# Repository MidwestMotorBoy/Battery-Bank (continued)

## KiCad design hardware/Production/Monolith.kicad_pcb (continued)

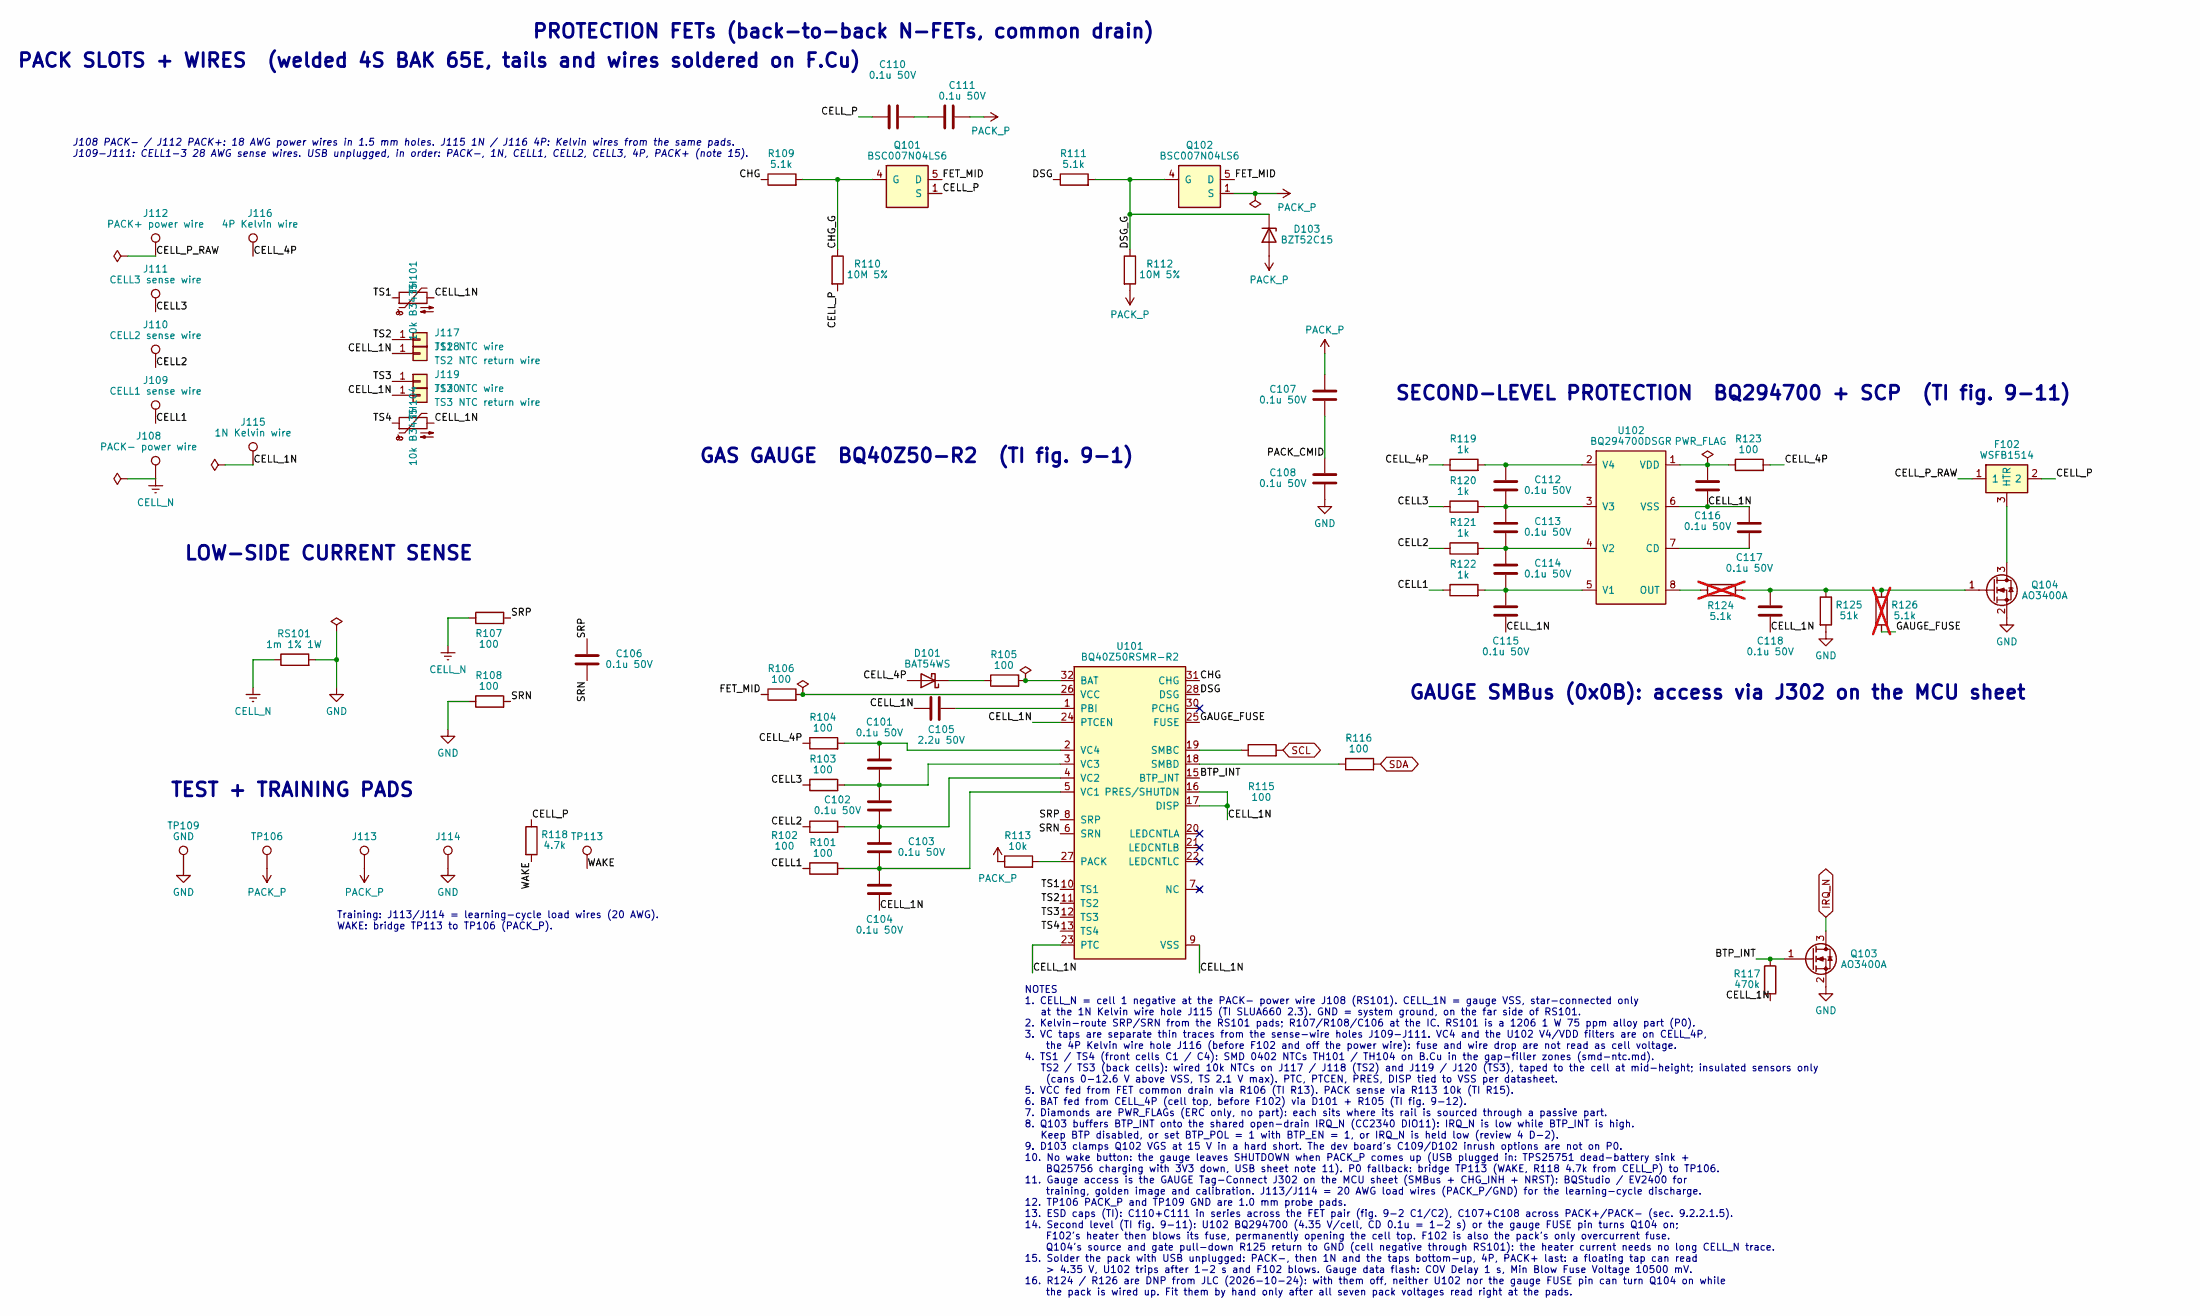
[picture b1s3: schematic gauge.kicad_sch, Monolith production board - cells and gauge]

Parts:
C101, C102, C103, C104, C106, C107, C108, C110, C111, C112, C113, C114, C115, C116, C117, C118: 0.1u 50V; C_0402_1005Metric; MPN CL05B104KB54PNC; LCSC C307331
C105: 2.2u 50V; C_0805_2012Metric; MPN CL21A225KBQNNNE; LCSC C377773
D101: BAT54WS; D_SOD-882; MPN BAT54L,315 (Nexperia); LCSC C549279
D103: BZT52C15; D_SOD-123; MPN BZT52C15 (JLC preferred C19077412); LCSC C19077412
F102: WSFB1514; TLC_WSFB_4x3mm; MPN TLC Electronic WSFB1514; LCSC C42463217
J108: PACK- power wire; SolderWire-18AWG_PTFE_1x01_D1.5mm_OD2.3mm
J109: CELL1 sense wire; SolderWire-28AWG_PTFE_1x01_D0.8mm_Pad1.5x1.4mm
J110: CELL2 sense wire; SolderWire-28AWG_PTFE_1x01_D0.8mm_Pad1.5x1.4mm
J111: CELL3 sense wire; SolderWire-28AWG_PTFE_1x01_D0.8mm_Pad1.5x1.4mm
J112: PACK+ power wire; SolderWire-18AWG_PTFE_1x01_D1.5mm_OD2.3mm
J113: LOAD PACK_P; SolderWire-0.5sqmm_1x01_D0.9mm_OD2.1mm
J114: LOAD GND; SolderWire-0.5sqmm_1x01_D0.9mm_OD2.1mm
J115: 1N Kelvin wire; SolderWire-28AWG_PTFE_1x01_D0.8mm_Pad1.5x1.4mm
J116: 4P Kelvin wire; SolderWire-28AWG_PTFE_1x01_D0.8mm_Pad1.5x1.4mm
J117: TS2 NTC wire; SolderWire-28AWG_PTFE_1x01_D0.8mm_Pad1.5x1.4mm
J118: TS2 NTC return wire; SolderWire-28AWG_PTFE_1x01_D0.8mm_Pad1.5x1.4mm
J119: TS3 NTC wire; SolderWire-28AWG_PTFE_1x01_D0.8mm_Pad1.5x1.4mm
J120: TS3 NTC return wire; SolderWire-28AWG_PTFE_1x01_D0.8mm_Pad1.5x1.4mm
Q101, Q102: BSC007N04LS6; Infineon_PG-TDSON-8_6.15x5.15mm_D5-8; MPN BSC007N04LS6ATMA1 (Infineon); LCSC C534274
Q103, Q104: AO3400A; SOT-23; MPN AO3400A (AOS); LCSC C20917
R101, R102, R103, R104, R105, R106, R107, R108, R123: 100; R_0402_1005Metric; MPN 0402WGF1000TCE; LCSC C25076
R109, R111: 5.1k; R_0402_1005Metric; MPN 0402WGF5101TCE; LCSC C25905
R110, R112: 10M 5%; R_0402_1005Metric; MPN 0402WGJ0106TCE; LCSC C26086
R113: 10k; R_0402_1005Metric; MPN 0402WGF1002TCE; LCSC C25744
R115, R116: 100; R_0201_0603Metric; MPN 0201WMF1000TEE; LCSC C270366
R117: 470k; R_0402_1005Metric; MPN 0402WGF4703TCE; LCSC C25790
R118: 4.7k; R_0402_1005Metric; MPN 0402WGF4701TCE; LCSC C25900
R119, R120, R121, R122: 1k; R_0402_1005Metric; MPN 0402WGF1001TCE; LCSC C11702
R124, R126: 5.1k; R_0402_1005Metric; MPN 0402WGF5101TCE; LCSC C25905; not fitted
R125: 51k; R_0402_1005Metric; MPN 0402WGF5102TCE; LCSC C25794
RS101: 1m 1% 1W; R_1206_3216Metric; MPN LR1206-21R001F4 (Ralec, 75 ppm); LCSC C154629
TH101, TH104: 10k B3435; R_0402_1005Metric; MPN NCP15XH103F03RC; LCSC C77131
TP106: PACK_P; TestPoint_Pad_D1.0mm
TP109: GND; TestPoint_Pad_D1.0mm; MPN RH-S2761-46R (ronghe; Harwin S2761-46R 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
TP113: WAKE; TestPoint_Pad_D1.0mm
U101: BQ40Z50RSMR-R2; TI_RSM0032A_VQFN-32_4x4mm_P0.4mm_EP1.4x1.4mm; MPN BQ40Z50RSMR-R2; LCSC C2845123
U102: BQ294700DSGR; Texas_DSG0008A_WSON-8-1EP_2x2mm_P0.5mm_EP0.9x1.6mm; MPN BQ294700DSGR; LCSC C414622

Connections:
/Cells and Gauge/BTP_INT: Q103.1 (G), R117.1, U101.15 (BTP_INT)
/Cells and Gauge/CELL1: J109.1 (1_1), R101.1, R122.1
/Cells and Gauge/CELL2: J110.1 (1_1), R102.1, R121.1
/Cells and Gauge/CELL3: J111.1 (1_1), R103.1, R120.1
/Cells and Gauge/CELL_1N: C104.2, C105.2, C115.2, C116.2, C117.1, C118.2, J115.1 (1_1), J118.1 (Pin_1_1), J120.1 (Pin_1_1), R117.2, TH101.2, TH104.2, U101.9 (VSS), U101.16 (PRES/SHUTDN), U101.17 (DISP), U101.23 (PTC), U101.24 (PTCEN), U101.33 (VSS), U102.6 (VSS), U102.9 (VSS)
/Cells and Gauge/CELL_4P: D101.2 (A), J116.1 (1_1), R104.1, R119.1, R123.2
/Cells and Gauge/CELL_P: C110.1, F102.2, Q101.1 (S), Q101.2 (S), Q101.3 (S), R110.2, R118.1
/Cells and Gauge/CELL_P_RAW: F102.1, J112.1 (1_1)
/Cells and Gauge/CHG: R109.1, U101.31 (CHG)
/Cells and Gauge/CHG_G: Q101.4 (G), R109.2, R110.1
/Cells and Gauge/DSG: R111.1, U101.28 (DSG)
/Cells and Gauge/DSG_G: D103.1 (K), Q102.4 (G), R111.2, R112.1
/Cells and Gauge/FET_MID: Q101.5 (D), Q101.6 (D), Q101.7 (D), Q101.8 (D), Q102.5 (D), Q102.6 (D), Q102.7 (D), Q102.8 (D), R106.1
/Cells and Gauge/GAUGE_FUSE: R126.2, U101.25 (FUSE)
/Cells and Gauge/PACK_CMID: C107.2, C108.1
/Cells and Gauge/SRN: C106.2, R108.2, U101.6 (SRN)
/Cells and Gauge/SRP: C106.1, R107.2, U101.8 (SRP)
/Cells and Gauge/TS1: TH101.1, U101.10 (TS1)
/Cells and Gauge/TS2: J117.1 (Pin_1_1), U101.11 (TS2)
/Cells and Gauge/TS3: J119.1 (Pin_1_1), U101.12 (TS3)
/Cells and Gauge/TS4: TH104.1, U101.13 (TS4)
/Cells and Gauge/WAKE: R118.2, TP113.1 (1_1)
CELL_N: J108.1 (1_1), R107.1, RS101.1
GND: C108.2, J114.1 (1_1), Q103.2 (S), Q104.2 (S), R108.1, R125.2, RS101.2, TP109.1 (1_1); also elsewhere on the board
IRQ_N: Q103.3 (D); also elsewhere on the board
unnamed: C110.2, C111.1
unnamed: D101.1 (K), R105.1
unnamed: F102.3 (HTR), Q104.3 (D)
unnamed: C118.1, Q104.1 (G), R124.2, R125.1, R126.1
unnamed: R105.2, U101.32 (BAT)
unnamed: R113.2, U101.27 (PACK)
unnamed: C105.1, U101.1 (PBI)
unnamed: R115.1, U101.19 (SMBC)
unnamed: R116.1, U101.18 (SMBD)
unnamed: C103.2, C104.1, R101.2, U101.5 (VC1)
unnamed: C102.2, C103.1, R102.2, U101.4 (VC2)
unnamed: C101.2, C102.1, R103.2, U101.3 (VC3)
unnamed: C101.1, R104.2, U101.2 (VC4)
unnamed: R106.2, U101.26 (VCC)
unnamed: C117.2, U102.7 (CD)
unnamed: R124.1, U102.8 (OUT)
unnamed: C114.2, C115.1, R122.2, U102.5 (V1)
unnamed: C113.2, C114.1, R121.2, U102.4 (V2)
unnamed: C112.2, C113.1, R120.2, U102.3 (V3)
unnamed: C112.1, R119.2, U102.2 (V4)
unnamed: C116.1, R123.1, U102.1 (VDD)
PACK_P: C107.1, C111.2, D103.2 (A), J113.1 (1_1), Q102.1 (S), Q102.2 (S), Q102.3 (S), R112.2, R113.1, TP106.1 (1_1); also elsewhere on the board
SCL: R115.2; also elsewhere on the board
SDA: R116.2; also elsewhere on the board

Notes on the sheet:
LOW-SIDE CURRENT SENSE
PACK SLOTS + WIRES (welded 4S BAK 65E, tails and wires soldered on F.Cu)
NOTES 1. CELL_N = cell 1 negative at the PACK- power wire J108 (RS101). CELL_1N = gauge VSS, star-connected only at the 1N Kelvin wire hole J115 (TI SLUA660 2.3). GND = system ground, on the far side of RS101. 2. Kelvin-route SRP/SRN from the RS101 pads; R107/R108/C106 at the IC. RS101 is a 1206 1 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
GAS GAUGE BQ40Z50-R2 (TI fig. 9-1)
SECOND-LEVEL PROTECTION BQ294700 + SCP (TI fig. 9-11)
J108 PACK- / J112 PACK+: 18 AWG power wires in 1.5 mm holes. J115 1N / J116 4P: Kelvin wires from the same pads. J109-J111: CELL1-3 28 AWG sense wires. USB unplugged, in order: PACK-, 1N, CELL1, CELL2, CELL3, 4P, PACK+ (note 15).
PROTECTION FETs (back-to-back N-FETs, common drain)
TEST + TRAINING PADS
Training: J113/J114 = learning-cycle load wires (20 AWG). WAKE: bridge TP113 to TP106 (PACK_P).
GAUGE SMBus (0x0B): access via J302 on the MCU sheet

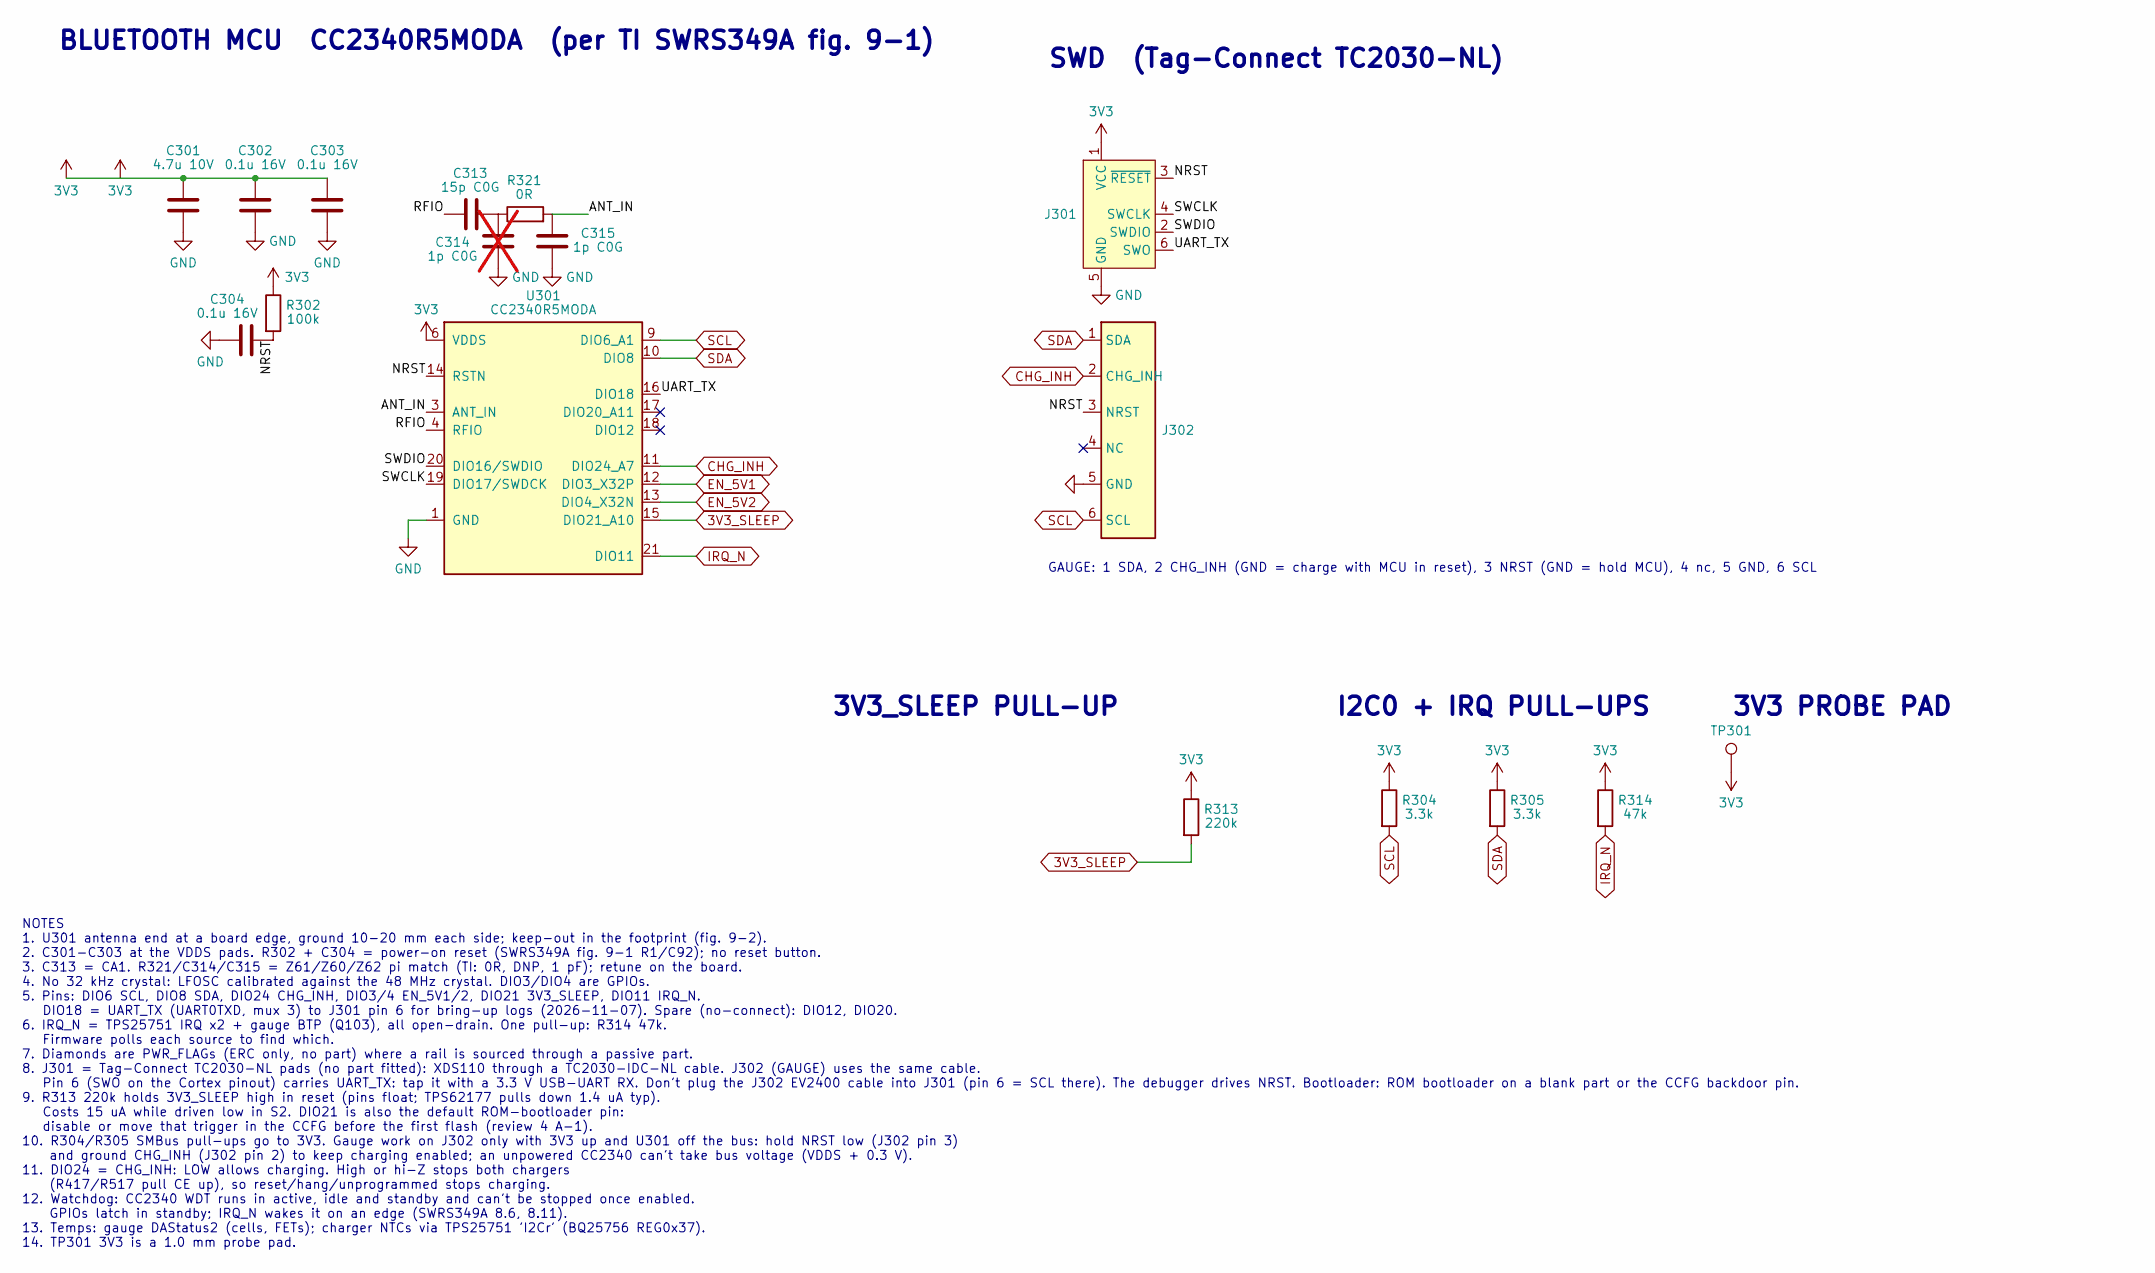
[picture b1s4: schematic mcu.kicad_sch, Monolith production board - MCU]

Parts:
C301: 4.7u 10V; C_0402_1005Metric; MPN CL05A475MP5NRNC; LCSC C23733
C302, C303, C304: 0.1u 16V; C_0201_0603Metric; MPN CL03A104KO3NNNC; LCSC C307380
C313: 15p C0G; C_0402_1005Metric; MPN 0402CG150J500NT; LCSC C1548
C314: 1p C0G; C_0402_1005Metric; MPN 0402CG1R0C500NT; LCSC C1550; not fitted
C315: 1p C0G; C_0402_1005Metric; MPN 0402CG1R0C500NT; LCSC C1550
J301: TC2030-NL; Tag-Connect_TC2030-IDC-NL_2x03_P1.27mm_Vertical
J302: TC2030-NL GAUGE; Tag-Connect_TC2030-IDC-NL_2x03_P1.27mm_Vertical
R302: 100k; R_0201_0603Metric; MPN 0201WMF1003TEE; LCSC C270364
R304, R305: 3.3k; R_0201_0603Metric; MPN 0201WMF3301TEE; LCSC C270350
R313: 220k; R_0201_0603Metric; MPN 0201WMF2203TEE; LCSC C473458
R314: 47k; R_0201_0603Metric; MPN 0201WMF4702TEE; LCSC C270345
R321: 0R; R_0402_1005Metric; MPN 0402WGF0000TCE; LCSC C17168
TP301: 3V3; TestPoint_Pad_D1.0mm
U301: CC2340R5MODA; TI_MHA0024A_CC2340R5MODA_7x10mm; MPN CC2340R5MODAN0MHAR

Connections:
3V3: C301.1, C302.1, C303.1, J301.1 (VCC), R302.1, R304.1, R305.1, R313.1, R314.1, TP301.1 (1_1), U301.6 (VDDS), U301.7 (VDDS); also elsewhere on the board
3V3_SLEEP: R313.2, U301.15 (DIO21_A10); also elsewhere on the board
/MCU/ANT_IN: C315.1, R321.2, U301.3 (ANT_IN)
/MCU/NRST: C304.1, J301.3 (~RESET), J302.3 (NRST), R302.2, U301.14 (RSTN)
/MCU/RFIO: C313.1, U301.4 (RFIO)
/MCU/SWCLK: J301.4 (SWCLK), U301.19 (DIO17/SWDCK)
/MCU/SWDIO: J301.2 (SWDIO), U301.20 (DIO16/SWDIO)
/MCU/UART_TX: J301.6 (SWO), U301.16 (DIO18)
CHG_INH: J302.2 (CHG_INH), U301.11 (DIO24_A7); also elsewhere on the board
EN_5V1: U301.12 (DIO3_X32P); also elsewhere on the board
EN_5V2: U301.13 (DIO4_X32N); also elsewhere on the board
GND: C301.2, C302.2, C303.2, C304.2, C314.2, C315.2, J301.5 (GND), J302.5 (GND), U301.1 (GND), U301.2 (GND), U301.5 (GND), U301.8 (GND), U301.22 (GND), U301.23 (GND), U301.24 (GND); also elsewhere on the board
IRQ_N: R314.2, U301.21 (DIO11); also elsewhere on the board
unnamed: C313.2, C314.1, R321.1
SCL: J302.6 (SCL), R304.2, U301.9 (DIO6_A1); also elsewhere on the board
SDA: J302.1 (SDA), R305.2, U301.10 (DIO8); also elsewhere on the board

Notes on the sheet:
NOTES 1. U301 antenna end at a board edge, ground 10-20 mm each side; keep-out in the footprint (fig. 9-2). 2. C301-C303 at the VDDS pads. R302 + C304 = power-on reset (SWRS349A fig. 9-1 R1/C92); no reset button. 3. C313 = CA1. R321/C314/C315 = Z61/Z60/Z62 pi match (TI: 0R, DNP, 1 pF); retune on th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
I2C0 + IRQ PULL-UPS
3V3_SLEEP PULL-UP
BLUETOOTH MCU CC2340R5MODA (per TI SWRS349A fig. 9-1)
3V3 PROBE PAD
GAUGE: 1 SDA, 2 CHG_INH (GND = charge with MCU in reset), 3 NRST (GND = hold MCU), 4 nc, 5 GND, 6 SCL
SWD (Tag-Connect TC2030-NL)

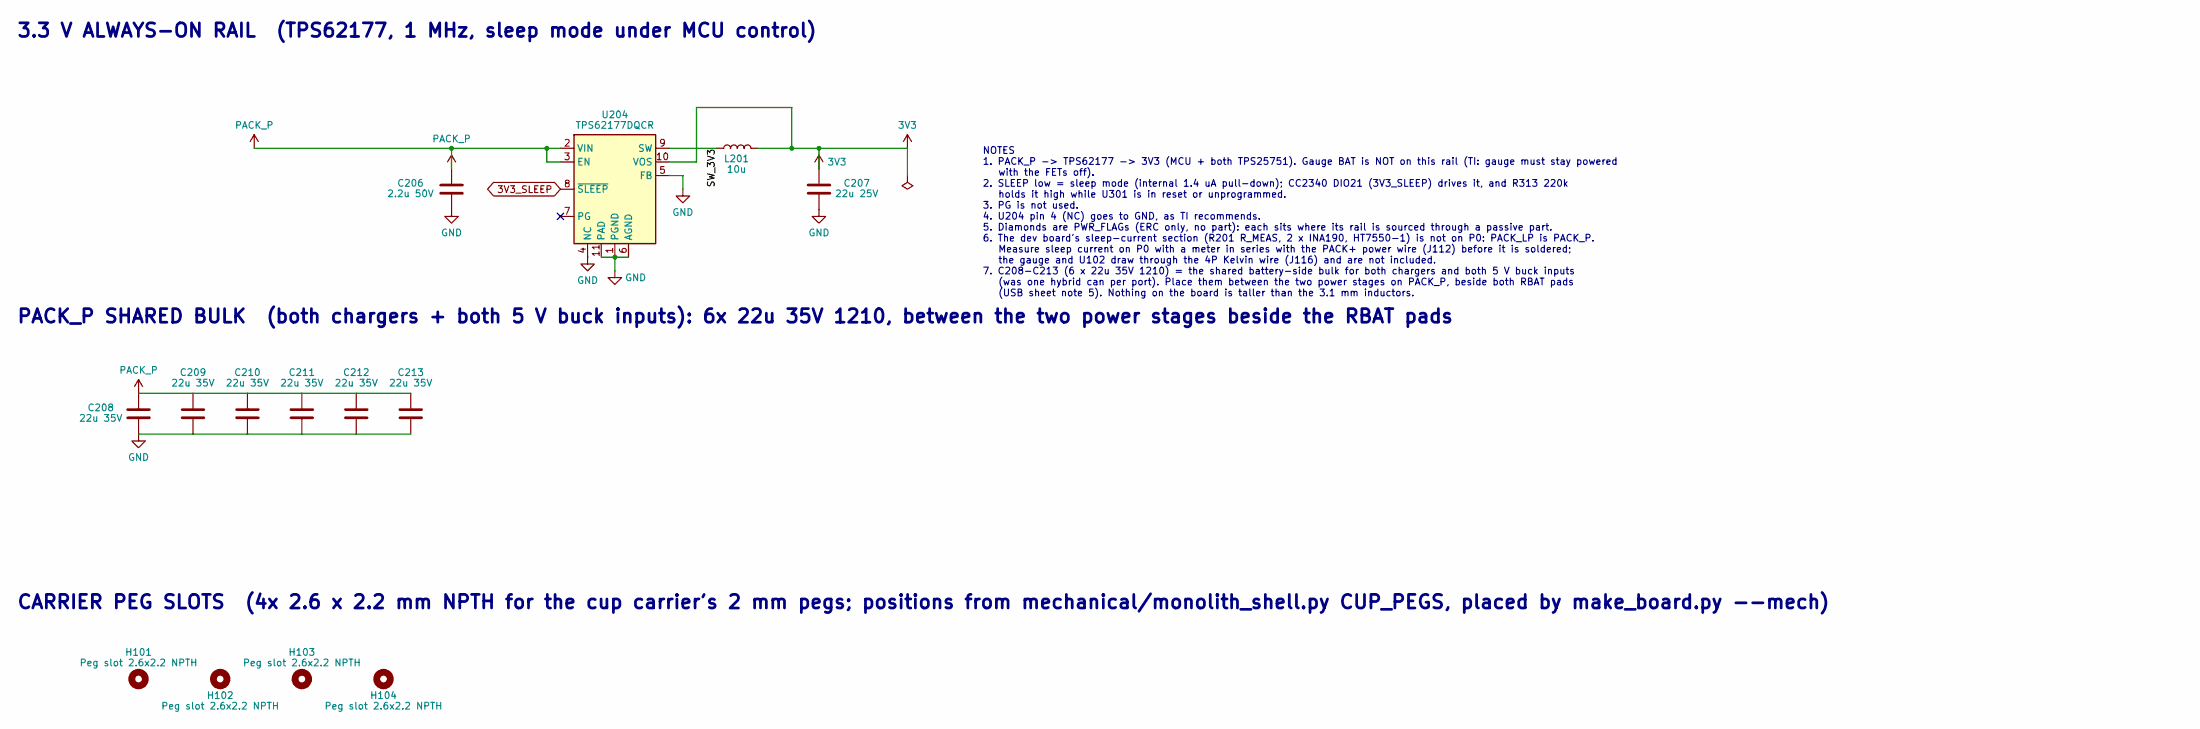
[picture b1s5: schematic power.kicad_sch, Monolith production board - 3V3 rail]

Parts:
C206: 2.2u 50V; C_0805_2012Metric; MPN CL21A225KBQNNNE; LCSC C377773
C207: 22u 25V; C_0805_2012Metric; MPN CL21A226MAQNNNE; LCSC C45783
C208, C209, C210, C211, C212, C213: 22u 35V; C_1210_3225Metric; MPN GMK325BJ226MM-P; LCSC C778721
H101, H102, H103, H104: Peg slot 2.6x2.2 NPTH; Peg_NPTH_Slot2.6x2.2mm
L201: 10u; L_Changjiang_FNR4030S; MPN FNR4030S100MT (Changjiang); LCSC C167879
U204: TPS62177DQCR; WSON-10-1EP_2x3mm_P0.5mm_EP0.84x2.4mm; MPN TPS62177DQCR; LCSC C91241

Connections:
3V3: C207.1, L201.2, U204.10 (VOS); also elsewhere on the board
3V3_SLEEP: U204.8 (~SLEEP); also elsewhere on the board
/3V3 Rail/SW_3V3: L201.1, U204.9 (SW)
GND: C206.2, C207.2, C208.2, C209.2, C210.2, C211.2, C212.2, C213.2, U204.1 (PGND), U204.4 (NC), U204.5 (FB), U204.6 (AGND), U204.11 (PAD); also elsewhere on the board
PACK_P: C206.1, C208.1, C209.1, C210.1, C211.1, C212.1, C213.1, U204.2 (VIN), U204.3 (EN); also elsewhere on the board

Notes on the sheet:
PACK_P SHARED BULK (both chargers + both 5 V buck inputs): 6x 22u 35V 1210, between the two power stages beside the RBAT pads
3.3 V ALWAYS-ON RAIL (TPS62177, 1 MHz, sleep mode under MCU control)
NOTES 1. PACK_P -> TPS62177 -> 3V3 (MCU + both TPS25751). Gauge BAT is NOT on this rail (TI: gauge must stay powered with the FETs off). 2. SLEEP low = sleep mode (internal 1.4 uA pull-down); CC2340 DIO21 (3V3_SLEEP) drives it, and R313 220k holds it high while U301 is in reset or unprogrammed. 3. 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
CARRIER PEG SLOTS (4x 2.6 x 2.2 mm NPTH for the cup carrier's 2 mm pegs; positions from mechanical/monolith_shell.py CUP_PEGS, placed by make_board.py --mech)

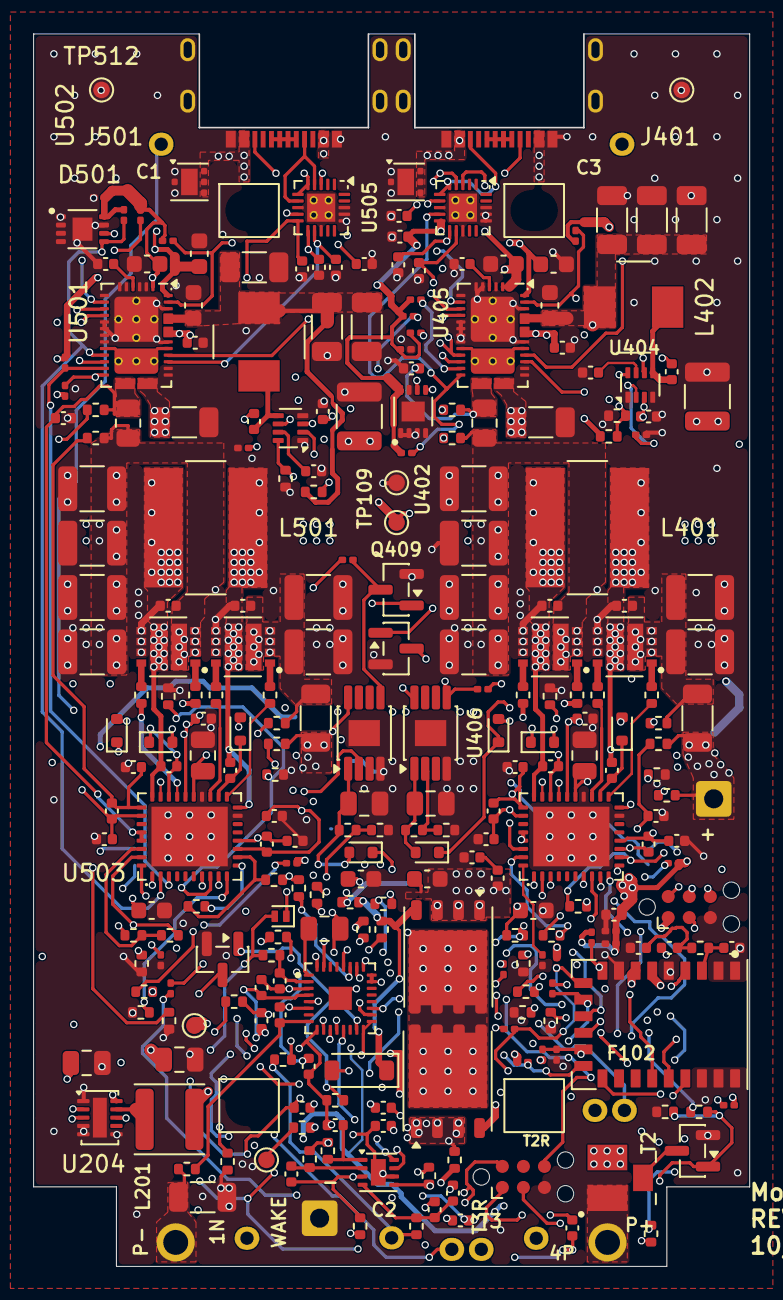
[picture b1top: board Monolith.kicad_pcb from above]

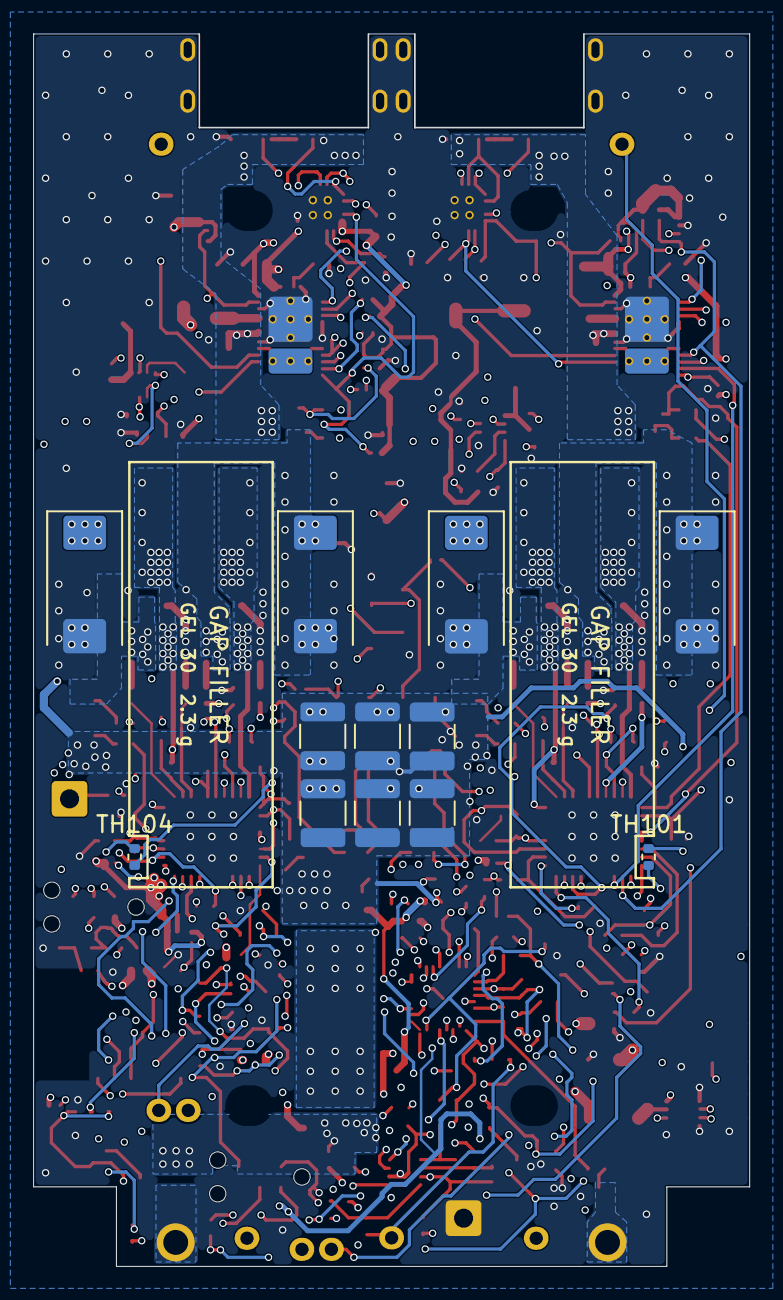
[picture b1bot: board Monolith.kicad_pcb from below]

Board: 6 copper layers, 43.2 x 74.4 mm, 289 parts (12 on the bottom side), 168 nets.

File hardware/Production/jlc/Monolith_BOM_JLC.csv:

Comment,Designator,Footprint,LCSC Part #,MPN,Qty
0.1u 50V,"C101,C102,C103,C104,C106,C107,C108,C110,C111,C112,C113,C114,C115,C116,C117,C118,C412,C413,C415,C416,C418,C419,C430,C438,C440,C446,C449,C451,C512,C513,C515,C516,C518,C519,C530,C538,C540,C546,C549,C551",C_0402_1005Metric,C307331,CL05B104KB54PNC,40
2.2u 50V,"C105,C206",C_0805_2012Metric,C377773,CL21A225KBQNNNE,2
22u 25V,"C207,C458,C558",C_0805_2012Metric,C45783,CL21A226MAQNNNE,3
22u 35V,"C208,C209,C210,C211,C212,C213,C420,C423,C424,C427,C431,C434,C444,C520,C523,C524,C527,C531,C534,C544",C_1210_3225Metric,C778721,GMK325BJ226MM-P,20
4.7u 10V,"C301,C410,C510",C_0402_1005Metric,C23733,CL05A475MP5NRNC,3
0.1u 16V,"C302,C303,C304,C408,C508",C_0201_0603Metric,C307380,CL03A104KO3NNNC,5
15p C0G,C313,C_0402_1005Metric,C1548,0402CG150J500NT,1
1p C0G,C315,C_0402_1005Metric,C1550,0402CG1R0C500NT,1
220p 50V,"C401,C402,C501,C502",C_0402_1005Metric,C1530,0402B221K500NT,4
10u 25V,"C403,C404,C407,C503,C504,C507",C_0603_1608Metric,C96446,CL10A106MA8NRNC,6
10u 6.3V,"C405,C505",C_0402_1005Metric,C15525,CL05A106MQ5NUNC,2
4.7u 50V,"C406,C506",C_1206_3216Metric,C29823,1206B475K500NT,2
1u 50V (VAC),"C409,C509",C_0603_1608Metric,C15849,CL10A105KB8NNNC,2
4.7u 25V,"C411,C511",C_0805_2012Metric,C1779,CL21A475KAQNNNE,2
0.47u 25V,"C414,C417,C514,C517",C_0402_1005Metric,C92361,CL05A474KA5NNNC,4
68u 35V,"C421,C456,C521,C556",CP_EIA-7343-31_Kemet-D,,KEMET T593V686M035APE070 (polymer tantalum),4
33n 50V,"C439,C539",C_0402_1005Metric,C7419416,FCC0402B333K500AT,2
22u 25V,"C441,C442,C443,C541,C542,C543",C_1206_3216Metric,C12891,CL31A226KAHNNNE,6
10n 50V,"C450,C550",C_0402_1005Metric,C15195,CL05B103KB5NNNC,2
1u 25V,"C452,C552",C_0402_1005Metric,C52923,CL05A105KA5NQNC,2
1u 50V,"C457,C557",C_0603_1608Metric,C15849,CL10A105KB8NNNC,2
BAT54WS,D101,D_SOD-882,C549279,"BAT54L,315 (Nexperia)",1
BZT52C15,D103,D_SOD-123,C19077412,BZT52C15 (JLC preferred C19077412),1
TVS2200DRVR,"D401,D501",WSON-6-1EP_2x2mm_P0.65mm_EP1x1.6mm,C55616459,TVS2200DRVR,2
LRB520S-40T1G,"D404,D405,D410,D411,D504,D505,D510,D511",D_SOD-523,C132124,LRB520S-40T1G,8
WSFB1514,F102,TLC_WSFB_4x3mm,C42463217,TLC Electronic WSFB1514,1
TYPE-C 16PCB1.6 IP68,"J401,J501",USB_C_Receptacle_ShouHan_TYPE-C_16PCB1.6_IP68,C55629729,TYPE-C 16PCB1.6 IP68 (Shou Han),2
10u,L201,L_Changjiang_FNR4030S,C167879,FNR4030S100MT (Changjiang),1
3.3u,"L401,L501",L_Coilank_APS0730,,XGL7030-332MEC (Coilcraft),2
3.3u,"L402,L502",L_COILMX_MS0520,C49248023,EHE05023R3MFB (ABC),2
BSC007N04LS6,"Q101,Q102",Infineon_PG-TDSON-8_6.15x5.15mm_D5-8,C534274,BSC007N04LS6ATMA1 (Infineon),2
AO3400A,"Q103,Q104,Q409,Q509",SOT-23,C20917,AO3400A (AOS),4
SiZ240DT,"Q401,Q402,Q501,Q502",Vishay_PowerPAIR_3x3S,C3289403,SiZ240DT-T1-GE3 (Vishay),4
100,"R101,R102,R103,R104,R105,R106,R107,R108,R123",R_0402_1005Metric,C25076,0402WGF1000TCE,9
5.1k,"R109,R111",R_0402_1005Metric,C25905,0402WGF5101TCE,2
10M 5%,"R110,R112",R_0402_1005Metric,C26086,0402WGJ0106TCE,2
10k,R113,R_0402_1005Metric,C25744,0402WGF1002TCE,1
100,"R115,R116",R_0201_0603Metric,C270366,0201WMF1000TEE,2
470k,R117,R_0402_1005Metric,C25790,0402WGF4703TCE,1
4.7k,R118,R_0402_1005Metric,C25900,0402WGF4701TCE,1
1k,"R119,R120,R121,R122",R_0402_1005Metric,C11702,0402WGF1001TCE,4
51k,R125,R_0402_1005Metric,C25794,0402WGF5102TCE,1
100k,"R302,R432,R441,R454,R455,R532,R541,R554,R555",R_0201_0603Metric,C270364,0201WMF1003TEE,9
3.3k,"R304,R305,R402,R403,R502,R503",R_0201_0603Metric,C270350,0201WMF3301TEE,6
220k,R313,R_0201_0603Metric,C473458,0201WMF2203TEE,1
47k,"R314,R417,R517",R_0201_0603Metric,C270345,0201WMF4702TEE,3
0R,"R321,R444,R445,R446,R447,R544,R545,R546,R547",R_0402_1005Metric,C17168,0402WGF0000TCE,9
10k,"R404,R504",R_0201_0603Metric,C473048,0201WMF1002TEE,2
137k 1%,"R409,R509",R_0402_1005Metric,C32298,0402WGF1373TCE,2
40.2k 1%,"R410,R452,R510,R552",R_0402_1005Metric,C25893,0402WGF4022TCE,4
10k 1%,"R411,R511",R_0402_1005Metric,C25744,0402WGF1002TCE,2
49.9k 1%,"R412,R512",R_0201_0603Metric,C7343965,RMCF0201FT49K9 (Stackpole),2
11.8k 1%,"R413,R513",R_0402_1005Metric,C93752,0402WGF1182TCE,2
3.6k 1%,"R414,R514",R_0402_1005Metric,C25891,0402WGF3601TCE,2
1.8k 1%,"R415,R515",R_0402_1005Metric,C25871,0402WGF1801TCE,2
5.6k 1%,"R416,R453,R516,R553",R_0402_1005Metric,C25908,0402WGF5601TCE,4
100k 0.1%,"R418,R518",R_0402_1005Metric,C445619,ERA2AEB104X,2
10.0k 0.1%,"R419,R519",R_0402_1005Metric,C191915,ERA2AEB103X,2
5m 0.5W,"R424,R524",R_0805_2012Metric,C728267,PA0805FRE470R005L,2
10R,"R425,R426,R428,R429,R525,R526,R528,R529",R_0402_1005Metric,C25077,0402WGF100JTCE,8
5m 1W (RBAT),"R427,R527",R_1206_3216Metric,C252653,MA120610FR005MZ (50 ppm),2
120k,"R433,R533",R_0402_1005Metric,C25750,0402WGF1203TCE,2
22k,"R434,R534",R_0402_1005Metric,C25768,0402WGF2202TCE,2
1k,"R435,R535",R_0201_0603Metric,C270365,0201WMF1001TEE,2
1m 1% 1W,RS101,R_1206_3216Metric,C154629,"LR1206-21R001F4 (Ralec, 75 ppm)",1
10k B3435,"TH101,TH104,TH401,TH501",R_0402_1005Metric,C77131,NCP15XH103F03RC,4
BQ40Z50RSMR-R2,U101,TI_RSM0032A_VQFN-32_4x4mm_P0.4mm_EP1.4x1.4mm,C2845123,BQ40Z50RSMR-R2,1
BQ294700DSGR,U102,Texas_DSG0008A_WSON-8-1EP_2x2mm_P0.5mm_EP0.9x1.6mm,C414622,BQ294700DSGR,1
TPS62177DQCR,U204,WSON-10-1EP_2x3mm_P0.5mm_EP0.84x2.4mm,C91241,TPS62177DQCR,1
CC2340R5MODA,U301,TI_MHA0024A_CC2340R5MODA_7x10mm,,CC2340R5MODAN0MHAR,1
TPS25751DREFR,"U401,U501",TI_WQFN-38-2EP_REF0038A_6x4mm_P0.4mm_2oz,C30169739,TPS25751DREFR,2
M24512-DFMC6TG,"U402,U502",ST_UFDFPN-8-1EP_2x3mm_P0.5mm_EP1.2x1.4mm,C222237,M24512-DFMC6TG,2
BQ25756RRVR,"U403,U503",TI_VQFN-36-1EP_RRV0036A_5x6mm_P0.5mm,C19272232,BQ25756RRVR,2
TPS62933DRLR,"U404,U504",SOT-583-8,C3200405,TPS62933DRLR,2
TPD6S300RUKR,"U405,U505",TI_RUK0020B_WQFN-20-1EP_3x3mm_P0.4mm_EP1.7x1.7mm_Via0.3,C2649810,TPD6S300RUKR (TI),2
TPS7A4101DGNR,"U406,U506",HVSSOP-8-1EP_3x3mm_P0.65mm_EP1.57x1.89mm,C111739,TPS7A4101DGNR (TI),2

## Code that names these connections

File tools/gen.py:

import csv
# (ref, part, value, package, status, [(pin, pin_name, net), ...])
C = "confirmed from TI datasheet"; A = "assumed, verify"; T = "to be selected"
parts = [
("U1","TPS25751D","USB-C PD controller","WQFN-38 4x6mm",C,[
 (1,"LDO_3V3","PD_3V3"),(2,"ADCIN1","ADCIN1"),(3,"ADCIN2","ADCIN2"),(4,"LDO_1V5","PD_1V5"),
 (5,"GPIO0","GND"),(6,"GPIO1","GND"),(7,"GPIO2","GND"),(8,"I2Ct_SDA","HOST_SDA"),(9,"I2Ct_SCL","HOST_SCL"),(10,"I2Ct_IRQ","HOST_IRQ"),
 (11,"GND","GND"),(12,"GND","GND"),(13,"GPIO11","GND"),(14,"GND","GND"),(15,"DRAIN","PD_DRAIN"),
 (16,"I2Cc_SDA","CHG_SDA"),(17,"I2Cc_SCL","CHG_SCL"),(18,"I2Cc_IRQ","CHG_INT"),(19,"GPIO3","GND"),
 (20,"PPHV","PPHV"),(21,"PPHV","PPHV"),(22,"PPHV","PPHV"),(23,"VBUS_IN","VBUS1"),(24,"VBUS_IN","VBUS1"),(25,"VBUS_IN","VBUS1"),
 (26,"GPIO4/USB_P","P1_DP"),(27,"GPIO5/USB_N","P1_DN"),(28,"CC1","P1_CC1"),(29,"CC2","P1_CC2"),(30,"DRAIN","PD_DRAIN"),(31,"GND","GND"),
 (32,"VBUS","VBUS1"),(33,"VBUS","VBUS1"),(34,"PP5V","5V"),(35,"PP5V","5V"),(36,"GPIO7","GND"),(37,"GPIO6","GND"),(38,"VIN_3V3","3V3"),
 ("EP1","GND pad","GND"),("EP2","DRAIN pad","PD_DRAIN")]),
("U2","BQ25756","Buck-boost charge controller","VQFN-36 5x6mm",C,[
 (1,"SCL","CHG_SCL"),(2,"SDA","CHG_SDA"),(3,"INT","CHG_INT"),(4,"STAT1","CHG_STAT1"),(5,"STAT2","CHG_STAT2"),(6,"PG","CHG_PG"),
 (7,"CE","CHG_CE_N"),(8,"TS","CHG_TS"),(9,"ICHG","CHG_ICHG"),(10,"ILIM_HIZ","CHG_ILIM"),(11,"FBG","CHG_FBG"),(12,"FB","CHG_FB"),
 (13,"SRN","VBAT_SYS"),(14,"SRP","BAT_SNS_P"),(15,"NC",""),(16,"NC",""),(17,"PGND","GND"),(18,"SW2","SW2"),(19,"HIDRV2","HG2"),
 (20,"BTST2","BTST2"),(21,"LODRV2","LG2"),(22,"PGND","GND"),(23,"DRV_SUP","REGN"),(24,"REGN","REGN"),(25,"LODRV1","LG1"),
 (26,"BTST1","BTST1"),(27,"HIDRV1","HG1"),(28,"SW1","SW1"),(29,"ACN","AC_SNS_N"),(30,"ACP","PPHV"),(31,"NC",""),
 (32,"VAC","CHG_VAC"),(33,"VAC","CHG_VAC"),(34,"ACUV","CHG_ACUV"),(35,"ACOV","CHG_ACOV"),(36,"FSW_SYNC","CHG_FSW"),("EP","Thermal pad","GND")]),
("Q1","N-FET 40V <=6mOhm logic-level","Buck high side","3.3x3.3mm",T,[("D","drain","AC_SNS_N"),("G","gate","HG1"),("S","source","SW1")]),
("Q2","N-FET 40V <=6mOhm logic-level","Buck low side","3.3x3.3mm",T,[("D","drain","SW1"),("G","gate","LG1"),("S","source","GND")]),
("Q3","N-FET 40V <=6mOhm logic-level","Boost low side","3.3x3.3mm",T,[("D","drain","SW2"),("G","gate","LG2"),("S","source","GND")]),
("Q4","N-FET 40V <=6mOhm logic-level","Boost high side","3.3x3.3mm",T,[("D","drain","BAT_SNS_P"),("G","gate","HG2"),("S","source","SW2")]),
("L1","Inductor","4.7uH, Isat>=12A, <=5mm tall","about 10x10mm",T,[(1,"","SW1"),(2,"","SW2")]),
("R1","Sense resistor","5mOhm 1% 1W","2512 or 1206 wide",A,[(1,"","PPHV"),(2,"","AC_SNS_N")]),
("R2","Sense resistor","5mOhm 1% 1W","2512 or 1206 wide",C,[(1,"","BAT_SNS_P"),(2,"","VBAT_SYS")]),
("C1","Bootstrap cap","100nF 25V","0402",A,[(1,"","BTST1"),(2,"","SW1")]),
("C2","Bootstrap cap","100nF 25V","0402",A,[(1,"","BTST2"),(2,"","SW2")]),
("C3","REGN cap","4.7uF 10V","0603",C,[(1,"","REGN"),(2,"","GND")]),
("C4","DRV_SUP cap","4.7uF 10V","0603",C,[(1,"","REGN"),(2,"","GND")]),
("C5","VAC cap","1uF 35V","0603",C,[(1,"","CHG_VAC"),(2,"","GND")]),
("R3","VAC feed","10 Ohm","0402",A,[(1,"","PPHV"),(2,"","CHG_VAC")]),
("C6-C9","Input bulk (port side)","4x 22uF 35V X7R, plus C10","1210",A,[(1,"","AC_SNS_N"),(2,"","GND")]),
("C10","Input bulk polymer","68uF 25V, <=5mm tall","D case",A,[(1,"","PPHV"),(2,"","GND")]),
("C11-C14","Output bulk (battery side)","4x 22uF 25V X7R, plus C15","1210",A,[(1,"","BAT_SNS_P"),(2,"","GND")]),
("C15","Battery bulk polymer","68uF 25V, <=5mm tall","D case",A,[(1,"","VBAT_SYS"),(2,"","GND")]),
("R4","FB top","243k 0.1%","0402",A,[(1,"","VBAT_SYS"),(2,"","CHG_FB")]),
("R5","FB bottom","24.9k 0.1%","0402",A,[(1,"","CHG_FB"),(2,"","CHG_FBG")]),
("R6","ICHG set","16.9k 1% (2.96A)","0402",C,[(1,"","CHG_ICHG"),(2,"","GND")]),
("R7","ILIM set","4.02k 1% (about 5A with 5mOhm R1)","0402",A,[(1,"","CHG_ILIM"),(2,"","GND")]),
("R8","FSW set","66.5k 1% (400kHz)","0402",C,[(1,"","CHG_FSW"),(2,"","GND")]),
("R9","TS upper","5.23k 1%","0402",C,[(1,"","REGN"),(2,"","CHG_TS")]),
("R10","TS lower","30.1k 1%","0402",C,[(1,"","CHG_TS"),(2,"","GND")]),
("RT1","NTC on cell","10k 103AT, on leads","wired",C,[(1,"","CHG_TS"),(2,"","GND")]),
("R11","ACUV/ACOV divider top","value from datasheet section 6.3","0402",T,[(1,"","CHG_VAC"),(2,"","CHG_ACOV")]),
("R12","ACUV/ACOV divider mid","value from datasheet section 6.3","0402",T,[(1,"","CHG_ACOV"),(2,"","CHG_ACUV")]),
("R13","ACUV/ACOV divider bottom","value from datasheet section 6.3","0402",T,[(1,"","CHG_ACUV"),(2,"","GND")]),
("R14","CE pull-down","10k","0402",A,[(1,"","CHG_CE_N"),(2,"","GND")]),
("R15","INT pull-up","10k","0402",C,[(1,"","CHG_INT"),(2,"","PD_3V3")]),
("R16","I2Cc SDA pull-up","3.3k","0402",C,[(1,"","CHG_SDA"),(2,"","PD_3V3")]),
("R17","I2Cc SCL pull-up","3.3k","0402",C,[(1,"","CHG_SCL"),(2,"","PD_3V3")]),
("R18","I2Ct SDA pull-up","4.7k","0402",C,[(1,"","HOST_SDA"),(2,"","3V3")]),
("R19","I2Ct SCL pull-up","4.7k","0402",C,[(1,"","HOST_SCL"),(2,"","3V3")]),
("R20","Host IRQ pull-up","10k","0402",A,[(1,"","HOST_IRQ"),(2,"","3V3")]),
("R21-R23","STAT1/STAT2/PG pull-ups","3x 100k","0402",A,[(1,"","CHG_STAT1 / CHG_STAT2 / CHG_PG"),(2,"","3V3")]),
("C16","LDO_3V3 cap","10uF 6.3V","0603",C,[(1,"","PD_3V3"),(2,"","GND")]),
("C17","LDO_1V5 cap","10uF 6.3V","0603",C,[(1,"","PD_1V5"),(2,"","GND")]),
("C18","VIN_3V3 cap","10uF 6.3V","0603",C,[(1,"","3V3"),(2,"","GND")]),
("C19","VBUS cap","4.7uF 35V","0805",C,[(1,"","VBUS1"),(2,"","GND")]),
("C20","PP5V cap","22uF 10V","0805",C,[(1,"","5V"),(2,"","GND")]),
("C21","CC1 cap","330pF","0402",C,[(1,"","P1_CC1"),(2,"","GND")]),
("C22","CC2 cap","330pF","0402",C,[(1,"","P1_CC2"),(2,"","GND")]),
("R24,R25","ADCIN1 strap divider","level chosen in TI GUI","0402",T,[(1,"","PD_3V3 / GND"),(2,"","ADCIN1")]),
("R26,R27","ADCIN2 strap divider","level chosen in TI GUI","0402",T,[(1,"","PD_3V3 / GND"),(2,"","ADCIN2")]),
("U3","I2C EEPROM","size and address per TPS25751 datasheet","SOT-23-5 or UDFN",T,[("SDA","","CHG_SDA"),("SCL","","CHG_SCL"),("VCC","","PD_3V3"),("GND","","GND")]),
("D1","VBUS TVS","TVS2200 or equivalent","SON",C,[(1,"","VBUS1"),(2,"","GND")]),
("D2","CC/D+/D- ESD array","4-channel, 24V-tolerant on CC","SOT/DFN",T,[("IO","","P1_CC1, P1_CC2, P1_DP, P1_DN"),("GND","","GND")]),
("J1","Amphenol 12402082E512A","Port 1 USB-C","vertical SMT",A,[("VBUS","A4/A9/B4/B9","VBUS1"),("GND","A1/A12/B1/B12/shell","GND"),("CC1","A5","P1_CC1"),("CC2","B5","P1_CC2"),("D+","A6/B6","P1_DP"),("D-","A7/B7","P1_DN")]),
]
blocks_pending = [("Protector","BQ77915 + 2 FETs + 5mOhm sense + 15A fuse","between cell stack and VBAT_SYS","pinout not yet pulled"),
 ("3.3V rail","TPS709 LDO","VBAT_SYS -> 3V3","pinout not yet pulled"),
 ("5V rail and port 2","TPS62933 buck, J2, 4.7k CC pull-ups","VBAT_SYS -> 5V, 5V -> VBUS2 through a load switch","pinout not yet pulled"),
 ("Bluetooth","Ebyte E104-BT5005A","HOST_SDA, HOST_SCL, HOST_IRQ, CHG_STAT1/2, CHG_PG, LEDs, SWD pads","pinout not yet pulled")]
with open("monolith_port1_netlist.csv","w",newline="") as f:
    w=csv.writer(f); w.writerow(["ref","part","value_or_role","pin","pin_name","net","status"])
    for ref,part,val,pkg,st,pins in parts:
        for p,n,net in pins: w.writerow([ref,part,val,p,n,net if net else "no connect",st])
with open("monolith_port1_bom.csv","w",newline="") as f:
    w=csv.writer(f); w.writerow(["ref","part","value_or_role","package","status","JLC_part_number"])
    for ref,part,val,pkg,st,pins in parts: w.writerow([ref,part,val,pkg,st,""])
    for b in blocks_pending: w.writerow(["(block)",b[1],b[0]+": "+b[2],"",b[3],""])
nets={}
for ref,part,val,pkg,st,pins in parts:
    for p,n,net in pins:
        if net: nets.setdefault(net,[]).append(f"{ref}.{p}")
single=[k for k,v in nets.items() if len(v)<2]
print(len(parts),"lines,",len(nets),"nets; single-node nets:",single)
print("FB:",1.536*(1+243/24.9), 1.566*(1+243/24.9), "ICHG:",50/16.9, "FSW R:",1/(10*400e3*5e-12-500e-9))

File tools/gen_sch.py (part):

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PINPOS["ESD_DUAL"] = {"1": (-5.08, 2.54, "L"), "2": (-5.08, -2.54, "L"), "3": (5.08, 0, "R")}
two("FUSE", "F"); two("LED", "D")
GNDP = [1, 2, 3, 4, 5, 8, 15, 17, 19, 21, 24, 31] + list(range(43, 78))
WBN = {6: "ANT_IN", 7: "ANT_OUT", 9: "PA4", 10: "PA8", 11: "PA1", 12: "PA6", 13: "PA2", 14: "PB8", 16: "VDDA", 18: "VBAT", 20: "VDDSMPS", 22: "BOOT0", 23: "NRST",
       25: "PB7", 26: "PB5", 27: "PB6", 28: "PA3", 29: "PA7", 30: "PA12", 32: "PA11", 33: "PB4", 34: "PA14", 35: "PA13", 36: "PA10", 37: "PA0", 38: "PA9", 39: "PA5",
       40: "PB1", 41: "PB0", 42: "PB2"}
ic("STM32WB1MMC", [(k, WBN[k]) for k in sorted(WBN)] + [(k, "VSSRF" if k in (5, 8) else "VSSSMPS" if k == 21 else "VSS") for k in GNDP])
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      16: "", 17: "", 18: "", 19: "P2_ATTACH", 20: "", "EP": "GND"}
place("TPS25810", "U8", "TPS25810", 127, 226.06, {str(k): v for k, v in p2.items()}, "pinout from TI datasheet; REF and REF_RTN order to confirm")
T = "TBD"
two_pin = [("L","L1","3.3uH MWSA1004S-3R3MT","SW1","SW2"),("R","R1","5m 1%","PPHV","AC_SNS_N"),("R","R2","5m 1%","BAT_SNS_P","VBAT_SYS"),
 ("C","C1","100n","BTST1","SW1"),("C","C2","100n","BTST2","SW2"),("C","C3","4.7u","REGN","GND"),("C","C4","4.7u","REGN","GND"),
 ("C","C5","1u 35V","CHG_VAC","GND"),("R","R3","10R","PPHV","CHG_VAC")]
two_pin += [("C",f"C{n}","22u 35V","AC_SNS_N","GND") for n in range(6,10)] + [("C","C10","68u 25V poly","PPHV","GND")]
two_pin += [("C",f"C{n}","22u 25V","BAT_SNS_P","GND") for n in range(11,15)] + [("C","C15","68u 25V poly","VBAT_SYS","GND")]
two_pin += [("R","R4","249k 0.1%","VBAT_SYS","CHG_FB"),("R","R5","25.5k 0.1%","CHG_FB","CHG_FBG"),("R","R6","16.9k","CHG_ICHG","GND"),
 ("R","R7","4.02k","CHG_ILIM","GND"),("R","R8","66.5k","CHG_FSW","GND"),("R","R9","5.23k","REGN","CHG_TS"),("R","R10","30.1k","CHG_TS","GND"),
 ("NTC","RT1","10k 103AT","CHG_TS","GND"),("R","R11","1M 1%","CHG_VAC","CHG_ACUV"),("R","R12","267k 1%","CHG_ACUV","CHG_ACOV"),("R","R13","66.5k 1%","CHG_ACOV","GND"),
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 ("C","C16","10u","PD_3V3","GND"),("C","C17","10u","PD_1V5","GND"),("C","C18","10u","3V3","GND"),("C","C19","4.7u 35V","VBUS1","GND"),
 ("C","C20","22u","5V","GND"),("C","C21","330p","P1_CC1","GND"),("C","C22","330p","P1_CC2","GND"),
 ("TVS","D1","TVS2200","VBUS1","GND")]
two_pin += [("FUSE","F1","15A","BAT_POS","VBAT_SYS"),("R","R30","33R","BAT_POS","PROT_VC4"),("R","R31","33R","CELL3","PROT_VC3"),("R","R32","33R","CELL2","PROT_VC2"),
 ("R","R33","33R","CELL1","PROT_VC1"),("R","R34","33R","BAT_NEG","PROT_VC0"),("C","C30","1u","PROT_VC4","PROT_VC3"),("C","C31","1u","PROT_VC3","PROT_VC2"),
 ("C","C32","1u","PROT_VC2","PROT_VC1"),("C","C33","1u","PROT_VC1","PROT_VC0"),("R","R35","1k","BAT_POS","PROT_VDD"),("C","C34","1u 35V","PROT_VDD","BAT_NEG"),
 ("C","C35","1u","PROT_AVDD","BAT_NEG"),("R","R36","3m 1% 1W","BAT_NEG","PROT_SNS"),("R","R37","4.53k","PROT_DSG","PROT_DSG_G"),("R","R38","1M","PROT_DSG_G","PROT_SNS"),
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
